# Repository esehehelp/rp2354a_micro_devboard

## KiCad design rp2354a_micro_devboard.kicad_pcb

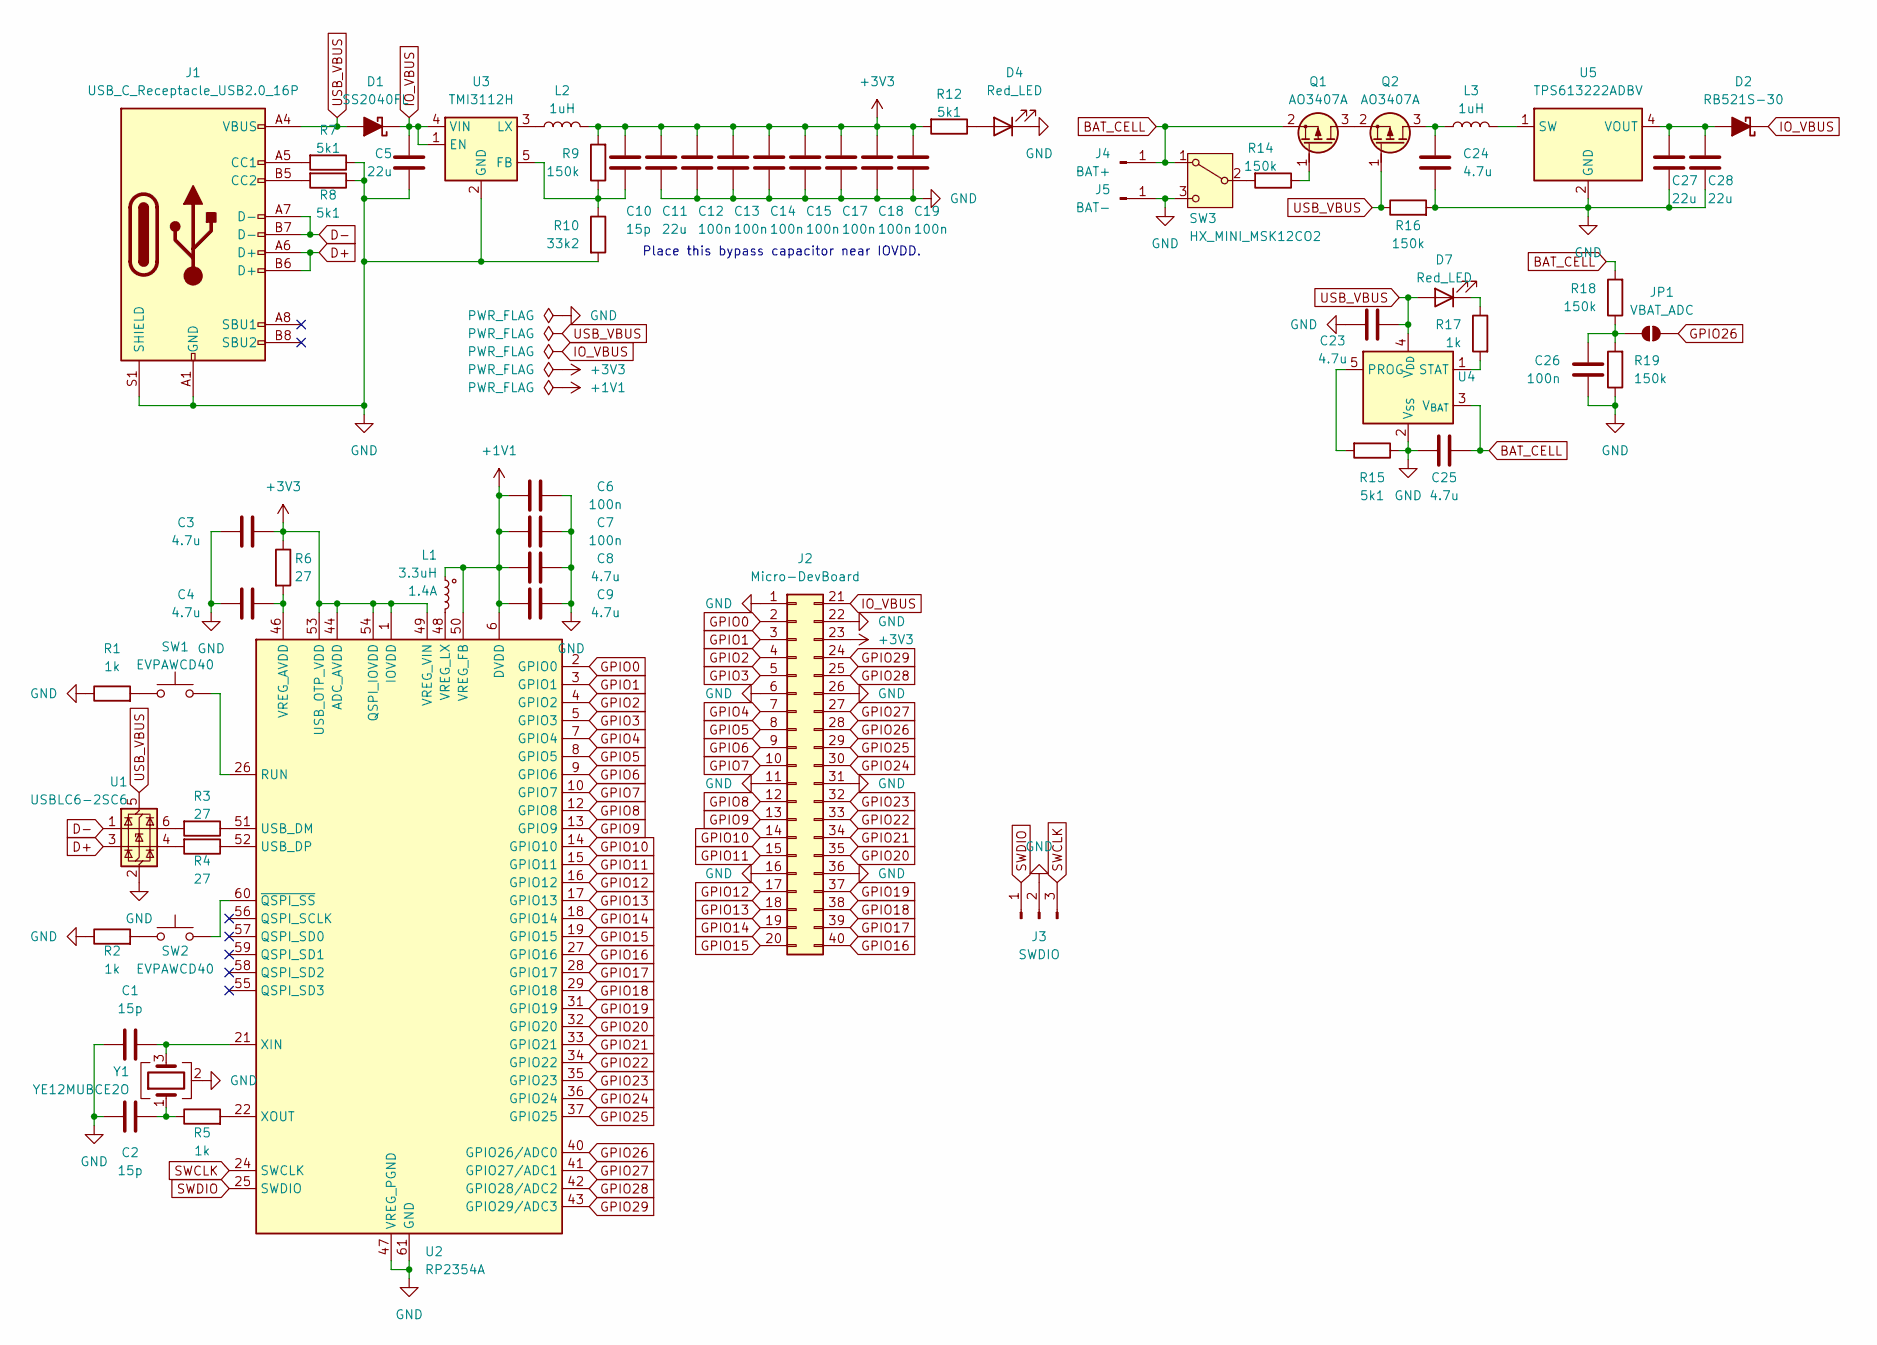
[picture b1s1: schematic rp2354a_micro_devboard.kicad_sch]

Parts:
C1, C2, C10: 15p; C_0402_1005Metric
C3, C4, C8, C9, C23, C24, C25: 4.7u; C_0402_1005Metric
C5, C11, C27, C28: 22u; C_0603_1608Metric
C6, C7, C12, C13, C14, C15, C17, C18, C19, C26: 100n; C_0402_1005Metric
D1: SS2040FL; D_SOD-123F
D2: RB521S-30; D_SOD-523
D4, D7: Red_LED; LED_0603_1608Metric
J1: USB_C_Receptacle_USB2.0_16P; USB_C_Receptacle_G-Switch_GT-USB-7010ASV
J2: Micro-DevBoard
J3: SWDIO; JST_SH_BM03B-SRSS-TB_1x03-1MP_P1.00mm_Vertical
J4: BAT+; SolderWirePad_1x01_SMD_1x2mm
J5: BAT-; SolderWirePad_1x01_SMD_1x2mm
JP1: VBAT_ADC; SolderJumper-2_P1.3mm_Open_Pad1.0x1.5mm
L1: 3.3uH; 0806_Polarized
L2, L3: 1uH; L_1008_2520Metric
Q1, Q2: AO3407A; SOT-23
R1, R2, R5, R17: 1k; R_0402_1005Metric
R3, R4, R6: 27; R_0402_1005Metric
R7, R8, R12, R15: 5k1; R_0402_1005Metric
R9, R14, R16, R18, R19: 150k; R_0402_1005Metric
R10: 33k2; R_0402_1005Metric
SW1, SW2: EVPAWCD40; SW_SPST_EVPAW
SW3: HX_MINI_MSK12CO2
U1: USBLC6-2SC6; SOT-23-6
U2: RP2354A; QFN-60-1EP_7x7mm_P0.4mm_EP3.4x3.4mm
U3: TMI3112H; SOT-23-5
U4: MCP73832-2-OT; SOT-23-5
U5: TPS613222ADBV; SOT-23-5
Y1: YE12MUBCE2O; Crystal_SMD_2016-4Pin_2.0x1.6mm

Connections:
+1V1: C6.1, C7.1, C8.1, C9.1, L1.1, U2.6 (DVDD), U2.23 (DVDD), U2.39 (DVDD), U2.50 (VREG_FB)
+3V3: C3.2, C10.2, C11.1, C12.1, C13.1, C14.1, C15.1, C17.1, C18.1, C19.1, J2.23, L2.2, R6.1, R9.2, R12.2, U2.1 (IOVDD), U2.11 (IOVDD), U2.20 (IOVDD), U2.30 (IOVDD), U2.38 (IOVDD), U2.44 (ADC_AVDD), U2.45 (IOVDD), U2.49 (VREG_VIN), U2.53 (USB_OTP_VDD), U2.54 (QSPI_IOVDD)
BAT_CELL: C25.1, J4.1, Q1.2 (S), R18.2, SW3.1 (A), U4.3 (V_{BAT})
D+: J1.A6 (D+), J1.B6 (D+), U1.3 (I/O2)
D-: J1.A7 (D-), J1.B7 (D-), U1.1 (I/O1)
GND: C1.1, C2.1, C3.1, C4.1, C5.2, C6.2, C7.2, C8.2, C9.2, C11.2, C12.2, C13.2, C14.2, C15.2, C17.2, C18.2, C19.2, C23.1, C24.2, C25.2, C26.2, C27.2, C28.2, D4.1 (K), J1.A1 (GND), J1.A12 (GND), J1.B1 (GND), J1.B12 (GND), J1.S1 (SHIELD), J2.1, J2.6, J2.11, J2.16, J2.22, J2.26, J2.31, J2.36, J3.2, J5.1, R1.1, R2.1, R7.1, R8.1, R10.2, R15.1, R16.2, R19.1, SW3.3 (C), U1.2 (GND), U2.47 (VREG_PGND), U2.61 (GND), U3.2 (GND), U4.2 (V_{SS}), U5.2 (GND), Y1.2 (G), Y1.4 (G)
GPIO0: J2.2, U2.2 (GPIO0)
GPIO1: J2.3, U2.3 (GPIO1)
GPIO2: J2.4, U2.4 (GPIO2)
GPIO3: J2.5, U2.5 (GPIO3)
GPIO4: J2.7, U2.7 (GPIO4)
GPIO5: J2.8, U2.8 (GPIO5)
GPIO6: J2.9, U2.9 (GPIO6)
GPIO7: J2.10, U2.10 (GPIO7)
GPIO8: J2.12, U2.12 (GPIO8)
GPIO9: J2.13, U2.13 (GPIO9)
GPIO10: J2.14, U2.14 (GPIO10)
GPIO11: J2.15, U2.15 (GPIO11)
GPIO12: J2.17, U2.16 (GPIO12)
GPIO13: J2.18, U2.17 (GPIO13)
GPIO14: J2.19, U2.18 (GPIO14)
GPIO15: J2.20, U2.19 (GPIO15)
GPIO16: J2.40, U2.27 (GPIO16)
GPIO17: J2.39, U2.28 (GPIO17)
GPIO18: J2.38, U2.29 (GPIO18)
GPIO19: J2.37, U2.31 (GPIO19)
GPIO20: J2.35, U2.32 (GPIO20)
GPIO21: J2.34, U2.33 (GPIO21)
GPIO22: J2.33, U2.34 (GPIO22)
GPIO23: J2.32, U2.35 (GPIO23)
GPIO24: J2.30, U2.36 (GPIO24)
GPIO25: J2.29, U2.37 (GPIO25)
GPIO26: J2.28, JP1.2 (B), U2.40 (GPIO26/ADC0)
GPIO27: J2.27, U2.41 (GPIO27/ADC1)
GPIO28: J2.25, U2.42 (GPIO28/ADC2)
GPIO29: J2.24, U2.43 (GPIO29/ADC3)
IO_VBUS: C5.1, D1.1 (K), D2.1 (K), J2.21, U3.1 (EN), U3.4 (VIN)
unnamed: C2.2, R5.1, Y1.1
unnamed: C27.1, C28.1, D2.2 (A), U5.4 (VOUT)
unnamed: D4.2 (A), R12.1
unnamed: D7.1 (K), R17.1
unnamed: J1.A5 (CC1), R7.2
unnamed: J1.B5 (CC2), R8.2
unnamed: C26.1, JP1.1 (A), R18.1, R19.2
unnamed: Q1.3 (D), Q2.2 (S)
unnamed: Q1.1 (G), R14.1
unnamed: C24.1, L3.1, Q2.3 (D)
unnamed: R1.2, SW1.1
unnamed: R2.2, SW2.1
unnamed: R3.2, U1.6 (I/O1)
unnamed: R4.2, U1.4 (I/O2)
unnamed: R14.2, SW3.2 (B)
unnamed: SW1.2, U2.26 (RUN)
unnamed: R3.1, U2.51 (USB_DM)
unnamed: R4.1, U2.52 (USB_DP)
unnamed: C4.2, R6.2, U2.46 (VREG_AVDD)
unnamed: L1.2, U2.48 (VREG_LX)
unnamed: C1.2, U2.21 (XIN), Y1.3
unnamed: R5.2, U2.22 (XOUT)
unnamed: SW2.2, U2.60 (~QSPI_SS)
unnamed: C10.1, R9.1, R10.1, U3.5 (FB)
unnamed: L2.1, U3.3 (LX)
unnamed: R15.2, U4.5 (PROG)
unnamed: R17.2, U4.1 (STAT)
unnamed: L3.2, U5.1 (SW)
SWCLK: J3.3, U2.24 (SWCLK)
SWDIO: J3.1, U2.25 (SWDIO)
USB_VBUS: C23.2, D1.2 (A), D7.2 (A), J1.A4 (VBUS), J1.A9 (VBUS), J1.B4 (VBUS), J1.B9 (VBUS), Q2.1 (G), R16.1, U1.5 (VBUS), U4.4 (V_{DD})

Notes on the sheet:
Place this bypass capacitor near IOVDD.

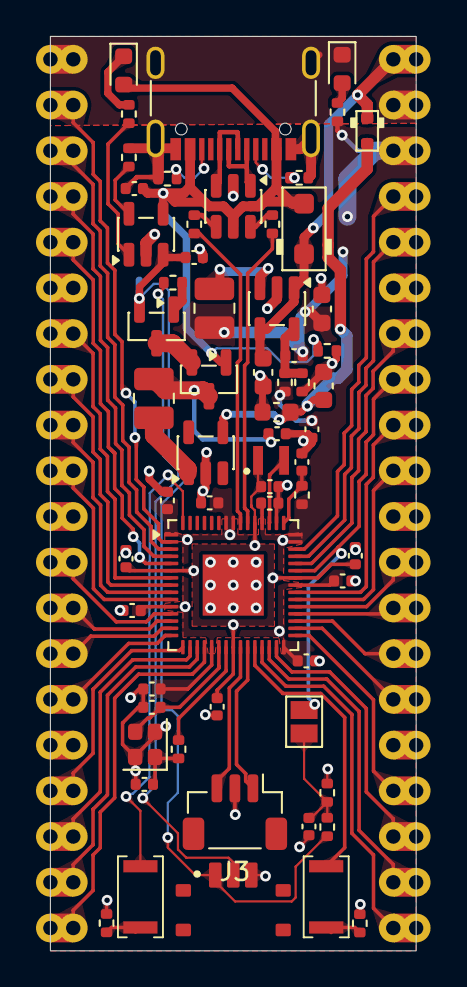
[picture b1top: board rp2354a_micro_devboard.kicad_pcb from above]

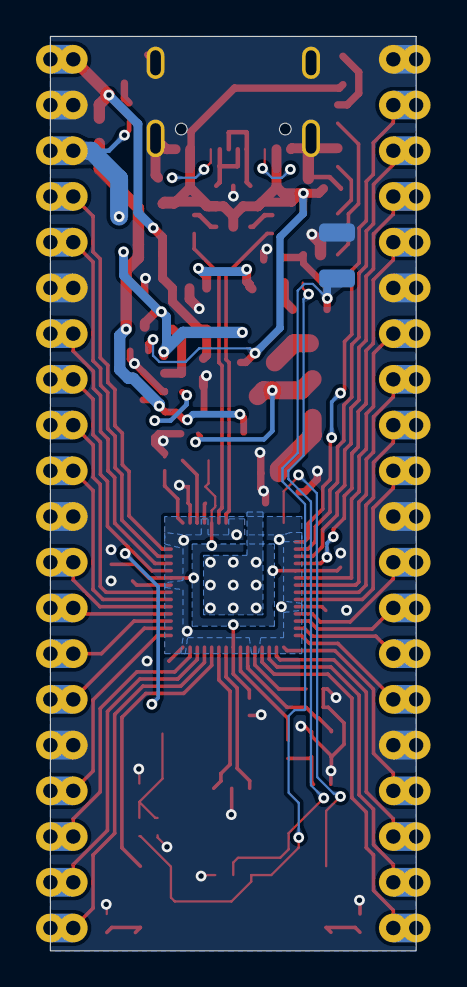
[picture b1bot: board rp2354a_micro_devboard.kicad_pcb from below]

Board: 2 copper layers, 20.3 x 50.8 mm, 65 parts (2 on the bottom side), 68 nets.

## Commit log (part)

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2026-06-29 Add KiCad project files
2026-06-30 feat: add battely charge&source. but kind to 1S-LiPo only.
